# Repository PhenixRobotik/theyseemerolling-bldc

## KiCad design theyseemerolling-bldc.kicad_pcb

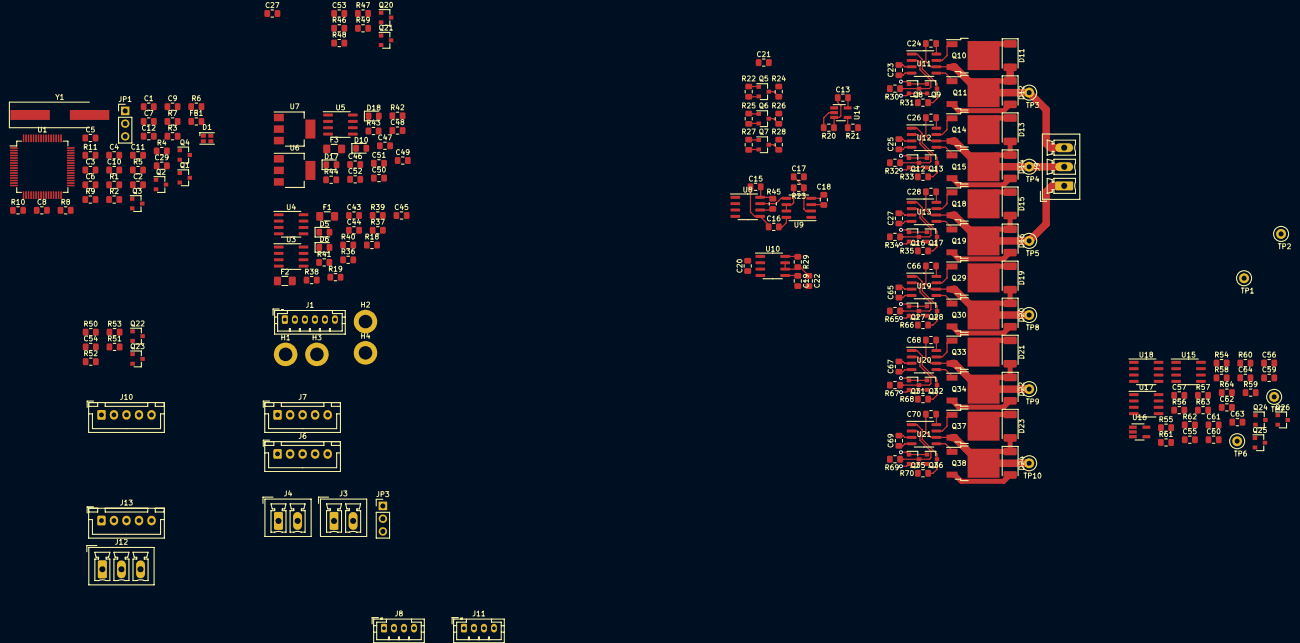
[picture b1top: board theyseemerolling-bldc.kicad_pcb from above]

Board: 2 copper layers, 228 parts (0 on the bottom side), 143 nets.

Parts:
C1, C2, C17, C22, C24, C26, C28, C59, C64, C66, C68, C70: C; C_0805_2012Metric_Pad1.15x1.40mm_HandSolder
C3, C6, C7, C8, C9, C10, C12, C13, C15, C16, C20, C21, C23, C25, C27, C27#2, C43, C44, C45, C47, C48, C55, C56, C57, C60, C63, C65, C67, C69: 100n; C_0805_2012Metric_Pad1.15x1.40mm_HandSolder
C4, C5: 2u2; C_0805_2012Metric_Pad1.15x1.40mm_HandSolder
C11: 4.7u -- 10u; C_0805_2012Metric_Pad1.15x1.40mm_HandSolder
C18, C19, C61, C62: 10n; C_0805_2012Metric_Pad1.15x1.40mm_HandSolder
C29: 1u; C_0805_2012Metric_Pad1.15x1.40mm_HandSolder
C46, C49, C50: 100p; C_0805_2012Metric_Pad1.15x1.40mm_HandSolder
C51, C52: 10u; C_0805_2012Metric_Pad1.15x1.40mm_HandSolder
C53, C54: 100nF; C_0805_2012Metric_Pad1.15x1.40mm_HandSolder
D1: LED_ARGB; LED_Cree-PLCC4_2x2mm_CW
D5, D6, D10, D17, D18: GREEN; LED_0805_2012Metric_Pad1.15x1.40mm_HandSolder
D11, D12, D13, D14, D15, D16, D19, D20, D21, D22, D23, D24: D_ALT; D_2010_5025Metric_Pad1.52x2.65mm_HandSolder
F1, F2: 5A; Fuse_1206_3216Metric_Pad1.42x1.75mm_HandSolder
F3: Polyfuse 2A; Fuse_1206_3216Metric_Pad1.42x1.75mm_HandSolder
FB1: Ferrite_Bead; L_0805_2012Metric_Pad1.15x1.40mm_HandSolder
H1, H2, H3, H4: MountingHole_Pad; MountingHole_2.7mm_M2.5_DIN965_Pad
J1: Conn_Debug; JST_PH_B6B-PH-K_1x06_P2.00mm_Vertical
J3: Power_1; PhoenixContact_MCV_1,5_2-G-3.81_1x02_P3.81mm_Vertical
J4: Power_2; PhoenixContact_MCV_1,5_2-G-3.81_1x02_P3.81mm_Vertical
J6, J7: CAN_conn; JST_XH_B5B-XH-A_1x05_P2.50mm_Vertical
J8, J11: Encoder_1; JST_PH_B4B-PH-K_1x04_P2.00mm_Vertical
J9, J12: M1; PhoenixContact_MCV_1,5_3-G-3.81_1x03_P3.81mm_Vertical
J10, J13: M1_hall; JST_XH_B5B-XH-A_1x05_P2.50mm_Vertical
JP1: JP_Select_Boot; PinHeader_1x03_P2.54mm_Vertical
JP3: Jumper_NC_Dual; PinHeader_1x03_P2.54mm_Vertical
Q1, Q2, Q3, Q4, Q5, Q6, Q7, Q8, Q9, Q12, Q13, Q16, Q17, Q20, Q21, Q22, Q23, Q24, Q25, Q26, Q27, Q28, Q31, Q32, Q35, Q36: BSS138; SOT-23
Q10, Q11, Q14, Q15, Q18, Q19, Q29, Q30, Q33, Q34, Q37, Q38: NMOS-T252; TO-252-2
R1, R2, R3, R4, R5, R6, R22, R24, R25, R26, R27, R28, R30, R31, R32, R33, R34, R35, R36, R38, R45, R46, R47, R48, R49, R50, R51, R52, R53, R54, R56, R57, R58, R59, R61, R62, R65, R66, R67, R68, R69, R70: 10k; R_0805_2012Metric_Pad1.15x1.40mm_HandSolder
R7: 91; R_0805_2012Metric_Pad1.15x1.40mm_HandSolder
R8: 27; R_0805_2012Metric_Pad1.15x1.40mm_HandSolder
R9: 39; R_0805_2012Metric_Pad1.15x1.40mm_HandSolder
R10, R11, R23, R29, R63, R64: R; R_0805_2012Metric_Pad1.15x1.40mm_HandSolder
R18, R19: 5k; R_0805_2012Metric_Pad1.15x1.40mm_HandSolder
R20, R55: 1k; R_0805_2012Metric_Pad1.15x1.40mm_HandSolder
R21, R60: 10; R_0805_2012Metric_Pad1.15x1.40mm_HandSolder
R37, R39: 1k2; R_0805_2012Metric_Pad1.15x1.40mm_HandSolder
R40: 3.3k; R_0805_2012Metric_Pad1.15x1.40mm_HandSolder
R41: 370; R_0805_2012Metric_Pad1.15x1.40mm_HandSolder
R42: 600; R_0805_2012Metric_Pad1.15x1.40mm_HandSolder
R43: 400; R_0805_2012Metric_Pad1.15x1.40mm_HandSolder
R44: 230; R_0805_2012Metric_Pad1.15x1.40mm_HandSolder
TP1, TP6: I1_max; TestPoint_Loop_D2.50mm_Drill1.0mm_LowProfile
TP2, TP7: over_current; TestPoint_Loop_D2.50mm_Drill1.0mm_LowProfile
TP3, TP4, TP5, TP8, TP9, TP10: Test_OUT; TestPoint_Loop_D2.50mm_Drill1.0mm_LowProfile
U1: STM32F405RGTx; LQFP-64_10x10mm_P0.5mm
U3, U9, U17: LM358; SOIC-8_3.9x4.9mm_P1.27mm
U4: LM317L_SO8; SOIC-8_3.9x4.9mm_P1.27mm
U5: TCAN332; SOIC-8_3.9x4.9mm_P1.27mm
U6: LD1117S50TR_SOT223; SOT-223-3_TabPin2
U7: LD1117S33TR_SOT223; SOT-223-3_TabPin2
U8, U15: ACS711xLCTR-12AB; SOIC-8_3.9x4.9mm_P1.27mm
U10, U18: LMC555xM; SOIC-8_3.9x4.9mm_P1.27mm
U11, U12, U13, U19, U20, U21: L6388E; SOIC-8_3.9x4.9mm_P1.27mm
U14, U16: SN74LVC1G32; SOT-23-5_HandSoldering
Y1: 8Mhz; Crystal_SMD_HC49-SD_HandSoldering

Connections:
+3V3: C6.2, C7.2, C8.2, C9.2, C10.2, C11.2, C13.1, C15.1, C16.2, C20.2, C43.1, C47.1, C52.1, C55.1, C56.2, C57.1, C63.2, D1.1, D18.2, FB1.1, JP1.3, Q5.1, Q6.1, Q7.1, Q20.1, Q21.1, Q22.1, Q23.1, Q24.1, Q25.1, Q26.1, R1.1, R2.1, R3.1, R4.1, R5.1, R22.2, R25.2, R27.2, R29.1, R45.1, R46.1, R47.2, R50.1, R51.2, R54.2, R57.2, R59.1, R61.2, R64.1, U1.1, U1.19, U1.32, U1.48, U1.64, U3.8, U5.3, U7.2, U8.8, U9.8, U10.4, U10.8, U14.5, U15.8, U16.5, U17.8, U18.4, U18.8
+5V: C21.2, C51.1, C53.2, C54.2, C60.2, D17.2, J8.1, J10.1, J11.1, J13.1, R24.2, R26.2, R28.2, R48.1, R49.2, R52.1, R53.2, R56.2, R58.2, R62.2, U6.2, U7.3
/CAN/7V_Input: F3.2, J6.5, J7.5
/CAN/+7V_CAN: C48.1, D10.2, F3.1, U6.3
/CAN/CAN_NRST: J6.2, J7.2, Q1.1, R1.2
/M1/Current: C17.1, R23.1, U1.17, U9.2
/M1/Current_fault: R45.2, U1.16, U8.6
/M1/H1: Q5.2, R22.1, U1.43
/M1/H2: Q6.2, R25.1, U1.44
/M1/H3: Q7.2, R27.1, U1.45
/M1/HVG1: R30.2, U1.30
/M1/HVG2: R32.2, U1.34
/M1/HVG3: R34.2, U1.36
/M1/LVG1: R31.2, U1.29
/M1/LVG2: R33.2, U1.33
/M1/LVG3: R35.2, U1.35
/M1/Phase_~EN: Q8.1, Q9.1, Q12.1, Q13.1, Q16.1, Q17.1, R21.1
/M1/bridge_output: D12.2, D14.2, D16.2, Q11.3, Q15.3, Q19.3, U8.1, U8.2
/M1/over_current: TP2.1, U10.3, U14.1
/M1/phase_1/Output: C24.2, D11.2, D12.1, J9.3, Q10.3, Q11.2, TP3.1, U11.6
/M1/phase_2/Output: C26.2, D13.2, D14.1, J9.2, Q14.3, Q15.2, TP4.1, U12.6
/M1/phase_3/Output: C28.2, D15.2, D16.1, J9.1, Q18.3, Q19.2, TP5.1, U13.6
/M2/Current: C59.1, R63.1, U1.20, U17.2
/M2/Current_fault: R59.2, U1.21, U15.6
/M2/H1: Q24.2, R54.1, U1.9
/M2/H2: Q25.2, R57.1, U1.10
/M2/H3: Q26.2, R61.1, U1.11
/M2/HVG1: R65.2, U1.25
/M2/HVG2: R67.2, U1.38
/M2/HVG3: R69.2, U1.40
/M2/LVG1: R66.2, U1.24
/M2/LVG2: R68.2, U1.37
/M2/LVG3: R70.2, U1.39
/M2/Phase_~EN: Q27.1, Q28.1, Q31.1, Q32.1, Q35.1, Q36.1, R60.1
/M2/bridge_output: D20.2, D22.2, D24.2, Q30.3, Q34.3, Q38.3, U15.1, U15.2
/M2/over_current: TP7.1, U16.1, U18.3
/M2/phase_1/Output: C66.2, D19.2, D20.1, J12.3, Q29.3, Q30.2, TP8.1, U19.6
/M2/phase_2/Output: C68.2, D21.2, D22.1, J12.2, Q33.3, Q34.2, TP9.1, U20.6
/M2/phase_3/Output: C70.2, D23.2, D24.1, J12.1, Q37.3, Q38.2, TP10.1, U21.6
/STM32/CAN1_RX: U1.61, U5.4
/STM32/CAN1_TX: C46.1, U1.62, U5.1
/STM32/DEBUG_RX: J1.5, U1.52
/STM32/DEBUG_TX: J1.6, U1.51
/STM32/Encoder_1_A: Q20.2, R46.2, U1.41
/STM32/Encoder_1_B: Q21.2, R47.1, U1.42
/STM32/Encoder_2_A: Q22.2, R50.2, U1.14
/STM32/Encoder_2_B: Q23.2, R51.1, U1.15
/STM32/M1_EN: R20.2, U1.22, U14.2
/STM32/M2_EN: R55.2, U1.23, U16.2
/STM32/Power_1_sense: U1.8, U3.1, U3.2
/STM32/Power_2_sense: U1.26, U3.6, U3.7
/STM32/SWCLK: J1.3, U1.49
/STM32/SWDIO: J1.4, U1.46
/STM32/SW_NRST: J1.2, Q2.1, R2.2
GND: C1.2, C2.2, C3.1, C4.2, C5.2, C6.1, C7.1, C8.1, C9.1, C10.1, C11.1, C12.1, C13.2, C15.2, C16.1, C17.2, C18.2, C19.2, C20.1, C21.1, C22.2, C23.1, C25.1, C27.1, C27#2.1, C29.1, C43.2, C44.2, C45.2, C46.2, C47.2, C48.2, C49.1, C50.2, C51.2, C52.2, C53.1, C54.1, C55.2, C56.1, C57.2, C59.2, C60.1, C61.2, C62.2, C63.1, C64.2, C65.1, C67.1, C69.1, H1.1, H2.1, H3.1, H4.1, J1.1, J3.1, J4.1, J6.1, J7.1, J8.3, J10.5, J11.3, J13.5, JP1.1, Q1.2, Q2.2, Q3.2, Q4.2, Q8.2, Q9.2, Q12.2, Q13.2, Q16.2, Q17.2, Q27.2, Q28.2, Q31.2, Q32.2, Q35.2, Q36.2, R18.2, R19.2, R20.1, R37.2, R39.2, R40.2, R42.2, R43.2, R44.2, R55.1, U1.12, U1.18, U1.63, U3.4, U5.2, U6.1, U7.1, U8.3, U8.4, U8.5, U9.4, U10.1, U11.4, U12.4, U13.4, U14.3, U15.3, U15.4, U15.5, U16.3, U17.4, U18.1, U19.4, U20.4, U21.4
unnamed: C1.1, R10.2, Y1.1
unnamed: C2.1, R11.2, Y1.2
unnamed: C3.2, Q3.3, Q4.3, R5.2, U1.7
unnamed: C4.1, U1.31
unnamed: C5.1, U1.47
unnamed: C18.1, TP1.1, U9.3
unnamed: C19.1, U10.5
unnamed: C22.1, R29.2, U10.6, U10.7
unnamed: C24.1, U11.8
unnamed: C26.1, U12.8
unnamed: C28.1, U13.8
unnamed: C45.1, JP3.1, R41.1, U4.2, U4.3, U4.6, U4.7
unnamed: C49.2, J6.4, J7.4, U5.7
unnamed: C50.1, J6.3, J7.3, U5.6
unnamed: C61.1, TP6.1, U17.3
unnamed: C62.1, U18.5
unnamed: C64.1, R64.2, U18.6, U18.7
unnamed: C66.1, U19.8
unnamed: C68.1, U20.8
unnamed: C70.1, U21.8
unnamed: D1.2, R7.1
unnamed: D1.3, R8.1
unnamed: D1.4, R9.1
unnamed: D5.1, R18.1
unnamed: D6.1, R19.1
unnamed: R36.2, R37.1, U3.3
unnamed: R38.2, R39.1, U3.5
unnamed: D10.1, R42.1
unnamed: D17.1, R43.1
unnamed: D18.1, R44.1
unnamed: F1.2, J3.2
unnamed: F2.2, J4.2
unnamed: J8.2, Q20.3, R48.2
unnamed: J8.4, Q21.3, R49.1
unnamed: J10.2, Q5.3, R24.1
unnamed: J10.3, Q6.3, R26.1
unnamed: J10.4, Q7.3, R28.1
unnamed: J11.2, Q22.3, R52.2
unnamed: J11.4, Q23.3, R53.1
unnamed: J13.2, Q24.3, R56.1
unnamed: J13.3, Q25.3, R58.1
unnamed: J13.4, Q26.3, R62.1
unnamed: JP1.2, R6.2
unnamed: Q1.3, Q3.1, R3.2
unnamed: Q2.3, Q4.1, R4.2
unnamed: Q8.3, R30.1, U11.2
unnamed: Q9.3, R31.1, U11.1
unnamed: Q10.1, U11.7
unnamed: Q11.1, U11.5
unnamed: Q12.3, R32.1, U12.2
unnamed: Q13.3, R33.1, U12.1
unnamed: Q14.1, U12.7
unnamed: Q15.1, U12.5
unnamed: Q16.3, R34.1, U13.2
unnamed: Q17.3, R35.1, U13.1
unnamed: Q18.1, U13.7
unnamed: Q19.1, U13.5
unnamed: Q27.3, R65.1, U19.2
unnamed: Q28.3, R66.1, U19.1
unnamed: Q29.1, U19.7
unnamed: Q30.1, U19.5
unnamed: Q31.3, R67.1, U20.2
unnamed: Q32.3, R68.1, U20.1
unnamed: Q33.1, U20.7
unnamed: Q34.1, U20.5
unnamed: Q35.3, R69.1, U21.2
unnamed: Q36.3, R70.1, U21.1
unnamed: Q37.1, U21.7
unnamed: Q38.1, U21.5
unnamed: R6.1, U1.60
unnamed: R7.2, U1.2
unnamed: R8.2, U1.3
unnamed: R9.2, U1.4
unnamed: R10.1, U1.5
unnamed: R11.1, U1.6
unnamed: R21.2, U14.4
unnamed: R23.2, U9.6, U9.7
unnamed: R40.1, R41.2, U4.4
unnamed: R60.2, U16.4
unnamed: R63.2, U17.6, U17.7
unnamed: U8.7, U9.5
unnamed: U9.1, U10.2
unnamed: U15.7, U17.5
unnamed: U17.1, U18.2
VDDA: C12.2, C29.2, FB1.2, U1.13
Vcc_1: C44.1, D5.2, D11.1, D13.1, D15.1, F1.1, Q10.2, Q14.2, Q18.2, R36.1, U4.1
Vcc_2: D6.2, D19.1, D21.1, D23.1, F2.1, Q29.2, Q33.2, Q37.2, R38.1
Vmos: C23.2, C25.2, C27.2, C27#2.2, C65.2, C67.2, C69.2, JP3.2, U11.3, U12.3, U13.3, U19.3, U20.3, U21.3

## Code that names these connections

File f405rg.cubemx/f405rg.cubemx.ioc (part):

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Mcu.Name=STM32F405RGTx
Mcu.Package=LQFP64
Mcu.UserName=STM32F405RGTx
PA0-WKUP.GPIOParameters=GPIO_Label
PA0-WKUP.GPIO_Label=Encoder_2_A
PA0-WKUP.Signal=S_TIM2_CH1_ETR
PA1.GPIOParameters=GPIO_Label
PA1.GPIO_Label=Encoder_2_B
PA1.Signal=S_TIM2_CH2
PA10.GPIOParameters=GPIO_Label
PA10.GPIO_Label=M1_H1
PA10.Signal=GPIO_Input
PA11.GPIOParameters=GPIO_Label
PA11.GPIO_Label=M1_H2
PA11.Signal=GPIO_Input
PA12.GPIOParameters=GPIO_Label
PA12.GPIO_Label=M1_H3
PA12.Signal=GPIO_Input
PA13.Mode=Serial_Wire
PA13.Signal=SYS_JTMS-SWDIO
PA14.Mode=Serial_Wire
PA14.Signal=SYS_JTCK-SWCLK
PA2.GPIOParameters=GPIO_Label
PA2.GPIO_Label=I1_fault
PA2.Signal=GPIO_Input
PA3.GPIOParameters=GPIO_Label
PA3.GPIO_Label=I1
PA3.Signal=ADCx_IN3
PA4.GPIOParameters=GPIO_Label
PA4.GPIO_Label=I2
PA4.Signal=ADCx_IN4
PA5.GPIOParameters=GPIO_Label
PA5.GPIO_Label=I2_fault
PA5.Signal=GPIO_Input
PA6.GPIOParameters=GPIO_Label
PA6.GPIO_Label=M1_EN
PA6.Signal=S_TIM3_CH1
PA7.GPIOParameters=GPIO_Label
PA7.GPIO_Label=M2_EN
PA7.Signal=S_TIM3_CH2
PA8.GPIOParameters=GPIO_Label
PA8.GPIO_Label=Encoder_1_A
PA8.Signal=S_TIM1_CH1
PA9.GPIOParameters=GPIO_Label
PA9.GPIO_Label=Encoder_1_B
PA9.Signal=S_TIM1_CH2
PB0.GPIOParameters=GPIO_Label
PB0.GPIO_Label=Power_2_sense
PB0.Signal=ADCx_IN8
PB10.GPIOParameters=GPIO_Label
PB10.GPIO_Label=M1_LVG_1
PB10.Signal=GPIO_Output
PB11.GPIOParameters=GPIO_Label
PB11.GPIO_Label=M1_HVG_1
PB11.Signal=GPIO_Output
PB12.GPIOParameters=GPIO_Label
PB12.GPIO_Label=M1_LVG_2
PB12.Signal=GPIO_Output
PB13.GPIOParameters=GPIO_Label
PB13.GPIO_Label=M1_HVG_2
PB13.Signal=GPIO_Output
PB14.GPIOParameters=GPIO_Label
PB14.GPIO_Label=M1_LVG_3
PB14.Signal=GPIO_Output
PB15.GPIOParameters=GPIO_Label
PB15.GPIO_Label=M1_HVG_3
PB15.Signal=GPIO_Output
PB8.Mode=Master
PB8.Signal=CAN1_RX
PB9.Mode=Master
PB9.Signal=CAN1_TX
PC0.GPIOParameters=GPIO_Label
PC0.GPIO_Label=Power_1_sense
PC0.Signal=ADCx_IN10
PC1.GPIOParameters=GPIO_Label
PC1.GPIO_Label=M2_H1
PC1.Signal=GPIO_Input
PC10.Mode=Asynchronous
PC10.Signal=UART4_TX
PC11.Mode=Asynchronous
PC11.Signal=UART4_RX
PC2.GPIOParameters=GPIO_Label
PC2.GPIO_Label=M2_H2
PC2.Signal=GPIO_Input
PC3.GPIOParameters=GPIO_Label
PC3.GPIO_Label=M2_H3
PC3.Signal=GPIO_Input
PC4.GPIOParameters=GPIO_Label
PC4.GPIO_Label=M2_LVG_1
PC4.Signal=GPIO_Output
PC5.GPIOParameters=GPIO_Label
PC5.GPIO_Label=M2_HVG_1
PC5.Signal=GPIO_Output
PC6.GPIOParameters=GPIO_Label
PC6.GPIO_Label=M2_LVG_2
PC6.Signal=GPIO_Output
PC7.GPIOParameters=GPIO_Label
PC7.GPIO_Label=M2_HVG_2
PC7.Signal=GPIO_Output
PC8.GPIOParameters=GPIO_Label
PC8.GPIO_Label=M2_LVG_3
PC8.Signal=GPIO_Output
PC9.GPIOParameters=GPIO_Label
PC9.GPIO_Label=M2_HVG_3
PC9.Signal=GPIO_Output
PH0-OSC_IN.Mode=HSE-External-Oscillator
PH0-OSC_IN.Signal=RCC_OSC_IN
PH1-OSC_OUT.Mode=HSE-External-Oscillator
PH1-OSC_OUT.Signal=RCC_OSC_OUT
RCC.HSE_VALUE=25000000
RCC.SYSCLKFreq_VALUE=25000000
RCC.SYSCLKSource=RCC_SYSCLKSOURCE_HSE
board=custom

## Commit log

2019-09-29 library init
2019-09-29 start of the beginning
2019-10-27 brushless control circuit
2019-10-27 forgot the capacito
2019-10-28 correction on bridge control
2019-10-28 Use subsheets for duplicate circuits, fix component in library, fix submodule url
2019-10-28 stm32 fisrt configuration
2019-10-28 Remove M1 tags in BLDC. Dedup encoders.
2019-10-29 added 2nd motor, wires and reset circuit
2019-10-29 corrections
2019-10-29 Add everything around stm32f405. Numerotation.
2019-10-29 oops, remove sheet
2019-10-29 fix wire
2019-10-30 Add footprint for most of the schematics
2019-10-30 Routing started
2019-10-31 Fix schematics, route
2019-10-31 Fix schematics, no warning left
2019-10-31 fix schematics -- finish
2019-10-31 update footprints, pcb
2019-11-07 post-lib update
